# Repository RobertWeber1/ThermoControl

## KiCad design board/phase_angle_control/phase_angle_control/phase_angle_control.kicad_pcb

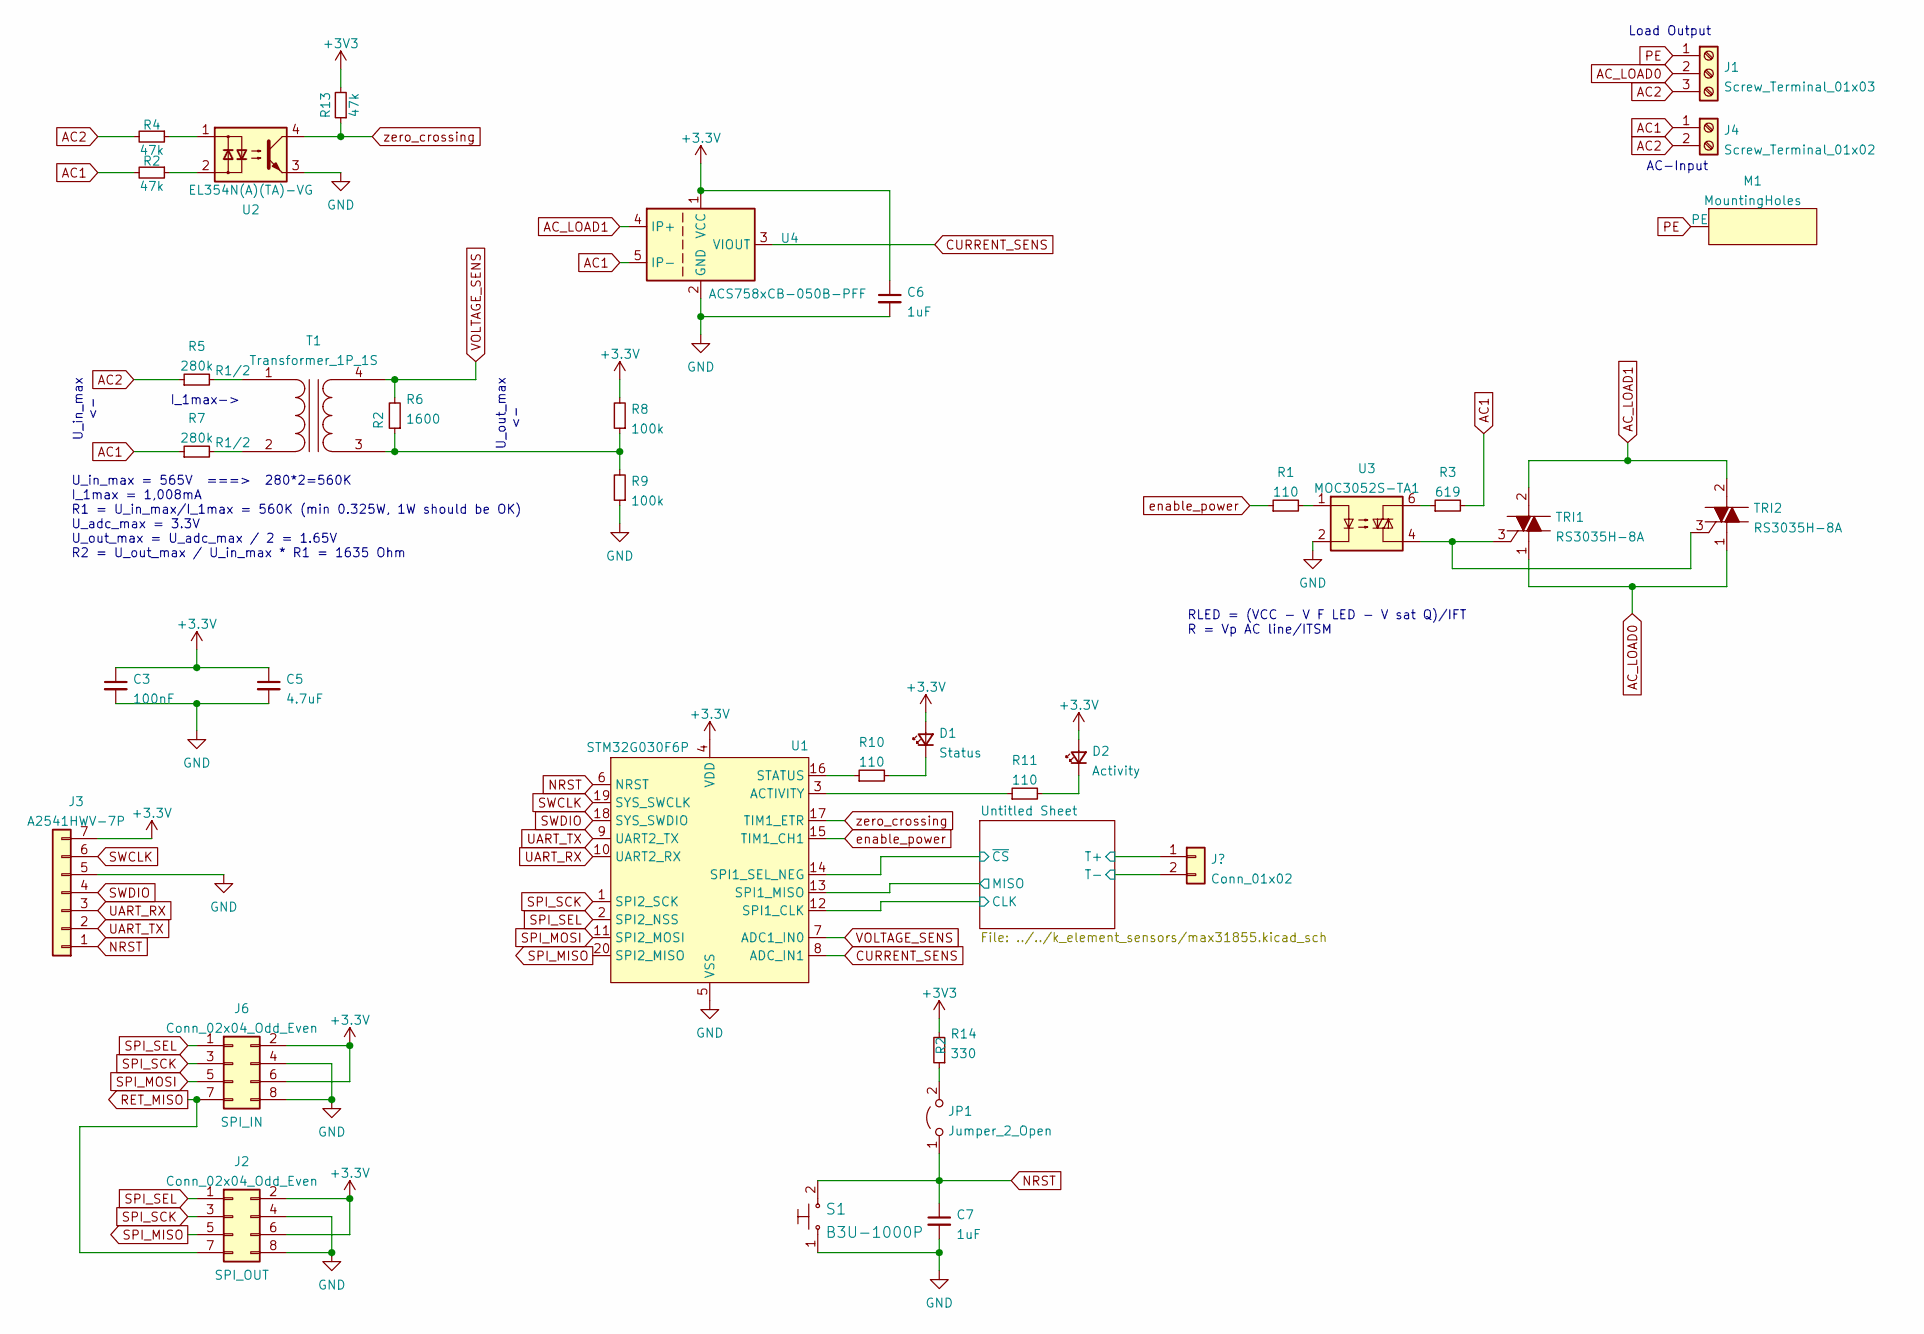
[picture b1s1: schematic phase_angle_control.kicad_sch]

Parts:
C3: 100nF; C_0603_1608Metric_Pad1.08x0.95mm_HandSolder; LCSC Part# C191538
C5: 4.7uF; C_0603_1608Metric_Pad1.08x0.95mm_HandSolder; LCSC Part# C651001
C6, C7: 1uF; C_0603_1608Metric_Pad1.08x0.95mm_HandSolder; LCSC Part# C393692
D1: Status; LED_0603_1608Metric_Pad1.05x0.95mm_HandSolder; LCSC Part# C273616
D2: Activity; LED_0603_1608Metric_Pad1.05x0.95mm_HandSolder; LCSC Part# C192667
J1: Screw_Terminal_01x03; KF206B-7.5-3P; LCSC Part# C475240
J2, J6: Conn_02x04_Odd_Even; PinHeader_2x04_P2.54mm_Horizontal; LCSC Part# C358706
J3: A2541HWV-7P; PinSocket_1x07_P2.54mm_Vertical; LCSC Part# C225504
J4: Screw_Terminal_01x02; KF206B-7.5-2P; LCSC Part# C475239
JP1: Jumper_2_Open; SolderJumper-2_P1.3mm_Open_RoundedPad1.0x1.5mm
M1: MountingHoles; MountingHolesPE
R1, R10, R11: 110; R_0603_1608Metric_Pad0.98x0.95mm_HandSolder; LCSC Part# C203247
R2: 47k; R_1206_3216Metric_Pad1.30x1.75mm_HandSolder; LCSC Part# C104822
R3: 619; R_1206_3216Metric_Pad1.30x1.75mm_HandSolder; LCSC Part# C247212
R4: 47k; R_1206_3216Metric_Pad1.30x1.75mm_HandSolder
R5, R7: 280k; R_1210_3225Metric_Pad1.30x2.65mm_HandSolder; LCSC Part# C422336
R6: 1600; R_0603_1608Metric_Pad0.98x0.95mm_HandSolder; LCSC Part# C186398
R8, R9: 100k; R_0603_1608Metric_Pad0.98x0.95mm_HandSolder; LCSC Part# C203223
R13: 47k; R_0603_1608Metric_Pad0.98x0.95mm_HandSolder; LCSC Part# C427281
R14: 330; R_0603_1608Metric_Pad0.98x0.95mm_HandSolder; LCSC Part# C186383
S1: B3U-1000P; Switch_Tactile_SMD_B3U-1000P; MPN B3U-1000P; Digi-Key_PN SW1020CT-ND
T1: Transformer_1P_1S; Transformer_ZMPT107-1; LCSC Part# C125191
TRI1, TRI2: RS3035H-8A; TO-220-3; MPN BTA16-600BWRG; LCSC Part# C246522
U1: STM32G030F6P; SSOP-20_4.4x6.5mm_P0.65mm; LCSC Part# C724040
U2: EL354N(A)(TA)-VG; SMDIP-4_W7.62mm; LCSC Part# C146213
U3: MOC3052S-TA1; DIP-6_W8.89mm_SMDSocket_LongPads; LCSC Part# C115471
U4: ACS758xCB-050B-PFF; Allegro_CB_PFF; LCSC Part# C73426

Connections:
/Untitled Sheet/CLK: U1.12 (SPI1_CLK); also elsewhere on the board
/Untitled Sheet/MISO: U1.13 (SPI1_MISO); also elsewhere on the board
/Untitled Sheet/~CS: U1.14 (SPI1_SEL_NEG); also elsewhere on the board
AC1: J4.1, R2.2, R3.2, R7.1, U4.5 (IP-)
AC2: J1.3, J4.2, R4.2, R5.1
AC_LOAD0: J1.2, TRI1.1 (A1), TRI2.1 (A1)
AC_LOAD1: TRI1.2 (A2), TRI2.2 (A2), U4.4 (IP+)
CURRENT_SENS: U1.8 (ADC_IN1), U4.3 (VIOUT)
GND: C3.2, C5.2, C6.2, C7.2, J2.4, J2.8, J3.5, J6.4, J6.8, R9.1, S1.1, U1.5 (VSS), U2.3, U3.2, U4.2 (GND); also elsewhere on the board
NRST: C7.1, J3.1, JP1.1 (A), S1.2, U1.6 (NRST)
unnamed: D1.1 (K), R10.2
unnamed: JP1.2 (B), R14.1
unnamed: R1.2, U3.1
unnamed: R2.1, U2.2
unnamed: R3.1, U3.6
unnamed: R4.1, U2.1
unnamed: R5.2, T1.1 (AA)
unnamed: R6.1, R8.1, R9.2, T1.3 (SA)
unnamed: R7.2, T1.2 (AB)
unnamed: R10.1, U1.16 (STATUS)
unnamed: R11.1, U1.3 (ACTIVITY)
unnamed: D2.1 (K), R11.2
unnamed: TRI1.3 (G), TRI2.3 (G), U3.4
PE: J1.1, M1.1 (PE)
RET_MISO: J2.7, J6.7
SPI_MISO: J2.5, U1.20 (SPI2_MISO)
SPI_MOSI: J6.5, U1.11 (SPI2_MOSI)
SPI_SCK: J2.3, J6.3, U1.1 (SPI2_SCK)
SPI_SEL: J2.1, J6.1, U1.2 (SPI2_NSS)
SWCLK: J3.6, U1.19 (SYS_SWCLK)
SWDIO: J3.4, U1.18 (SYS_SWDIO)
UART_RX: J3.3, U1.10 (UART2_RX)
UART_TX: J3.2, U1.9 (UART2_TX)
VOLTAGE_SENS: R6.2, T1.4 (SB), U1.7 (ADC1_IN0)
enable_power: R1.1, U1.15 (TIM1_CH1)
zero_crossing: R13.1, U1.17 (TIM1_ETR), U2.4

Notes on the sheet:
U_in_max = 565V ===> 280*2=560K I_1max = 1,008mA R1 = U_in_max/I_1max = 560K (min 0.325W, 1W should be OK) U_adc_max = 3.3V U_out_max = U_adc_max / 2 = 1.65V R2 = U_out_max / U_in_max * R1 = 1635 Ohm
U_in_max <-
I_1max->
U_out_max <-
RLED = (VCC - V F LED - V sat Q)/IFT R = Vp AC line/ITSM
Load Output
AC-Input

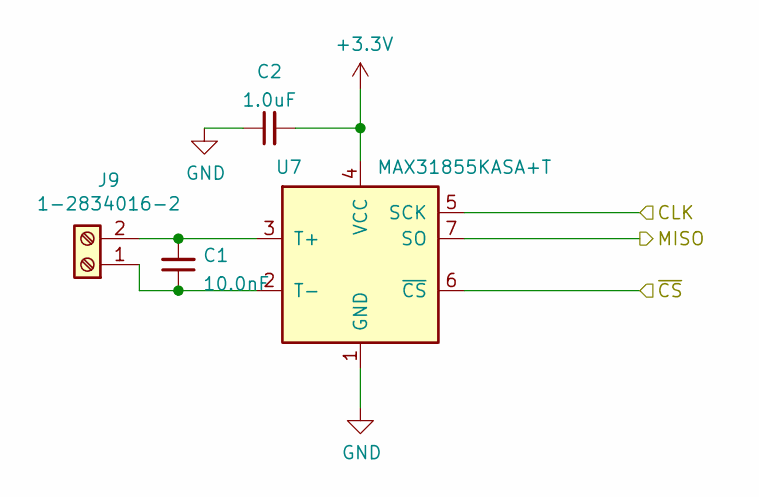
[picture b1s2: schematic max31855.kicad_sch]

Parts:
C1: 10.0nF; C_0603_1608Metric_Pad1.08x0.95mm_HandSolder; LCSC Part# C389113
C2: 1.0uF; C_0603_1608Metric_Pad1.08x0.95mm_HandSolder; LCSC Part# C328910
J9: 1-2834016-2; con_A123829-ND‎; LCSC Part # C474892
U7: MAX31855KASA+T; SOIC-8_3.9x4.9mm_P1.27mm; LCSC Part# C52028

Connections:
/Untitled Sheet/CLK: U7.5 (SCK); also elsewhere on the board
/Untitled Sheet/MISO: U7.7 (SO); also elsewhere on the board
/Untitled Sheet/~CS: U7.6 (~CS); also elsewhere on the board
GND: C2.1, U7.1 (GND); also elsewhere on the board
unnamed: C1.1, J9.1, U7.2 (T-)
unnamed: C1.2, J9.2, U7.3 (T+)

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
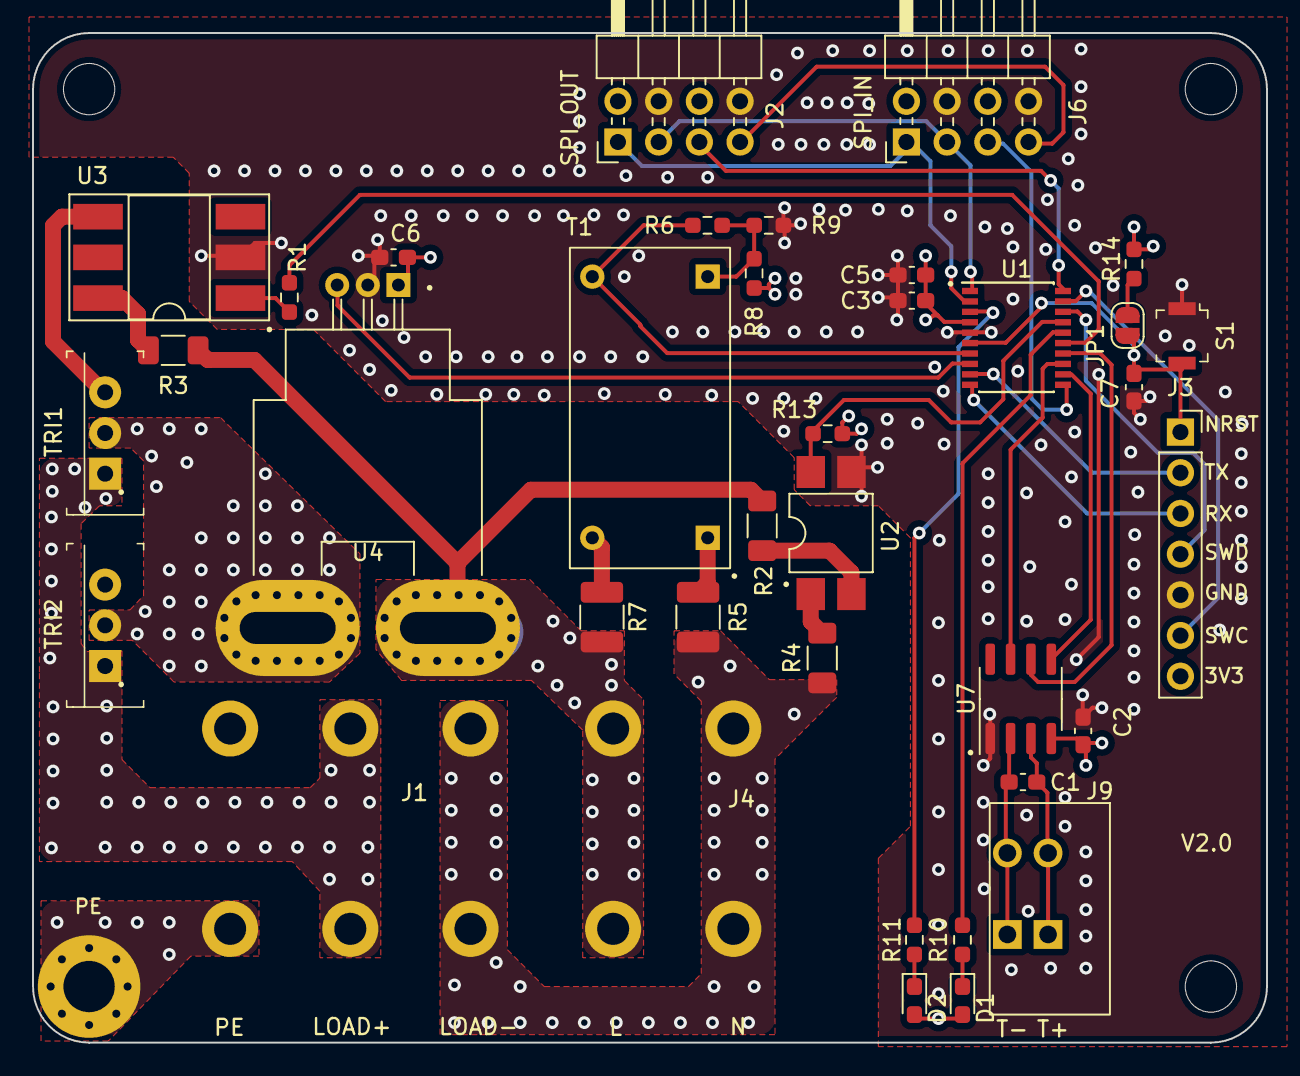
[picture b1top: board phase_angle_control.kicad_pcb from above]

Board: 4 copper layers, 77.0 x 63.0 mm, 38 parts (0 on the bottom side), 39 nets.

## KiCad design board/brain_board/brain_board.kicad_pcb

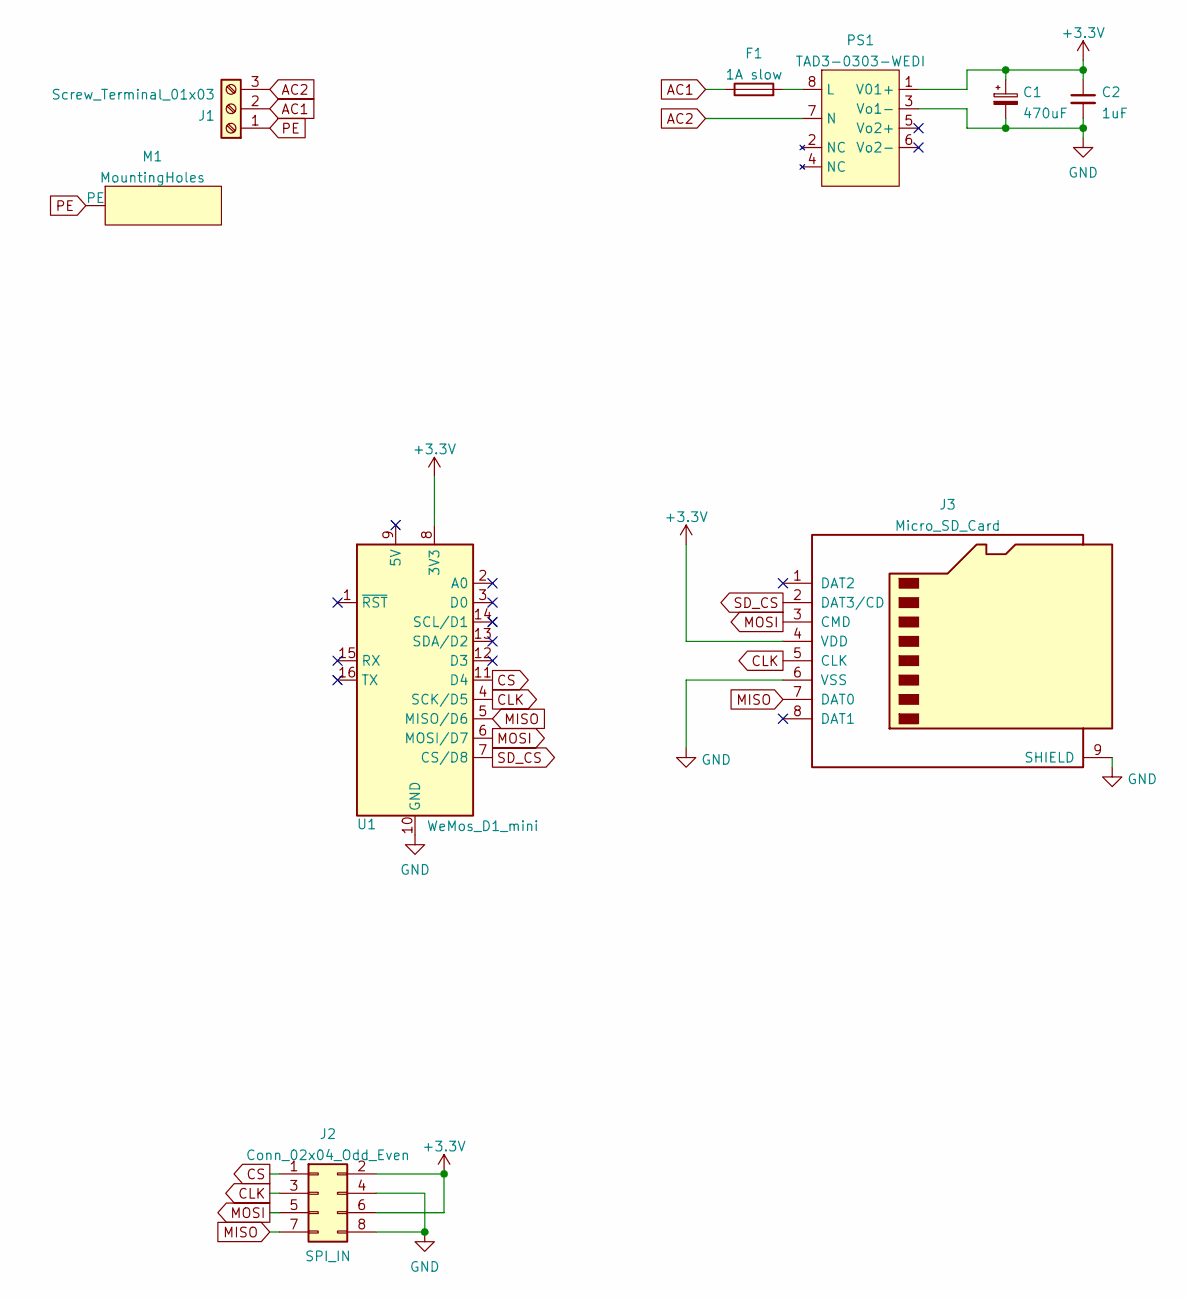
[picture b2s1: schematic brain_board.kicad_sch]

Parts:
C1: 470uF; CP_Radial_D8.0mm_P3.50mm; LCSC Part# C840136
C2: 1uF; C_Disc_D4.3mm_W1.9mm_P5.00mm; LCSC Part# C444742
F1: 1A slow; Fuse_2410; LCSC Part# C136380
J1: Screw_Terminal_01x03; KF206B-7.5-3P; LCSC Part# C475240
J2: Conn_02x04_Odd_Even; PinHeader_2x04_P2.54mm_Horizontal; LCSC Part# C358706
J3: Micro_SD_Card; micro_sd_slot; LCSC Part# C341095
M1: MountingHoles; MountingHolesPE
PS1: TAD3-0303-WEDI; LCSC Part# C695893
U1: WeMos_D1_mini; WEMOS_D1_mini_light

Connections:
+3V3: C1.1, C2.1, J2.2, J2.6, J3.4 (VDD), PS1.1 (V01+), U1.8 (3V3)
AC1: F1.1, J1.2
AC2: J1.3, PS1.7 (N)
CLK: J2.3, J3.5 (CLK), U1.4 (SCK/D5)
CS: J2.1, U1.11 (D4)
GND: C1.2, C2.2, J2.4, J2.8, J3.6 (VSS), J3.9 (SHIELD), PS1.3 (Vo1-), U1.10 (GND)
MISO: J2.7, J3.7 (DAT0), U1.5 (MISO/D6)
MOSI: J2.5, J3.3 (CMD), U1.6 (MOSI/D7)
unnamed: F1.2, PS1.8 (L)
PE: J1.1, M1.1 (PE)
SD_CS: J3.2 (DAT3/CD), U1.7 (CS/D8)

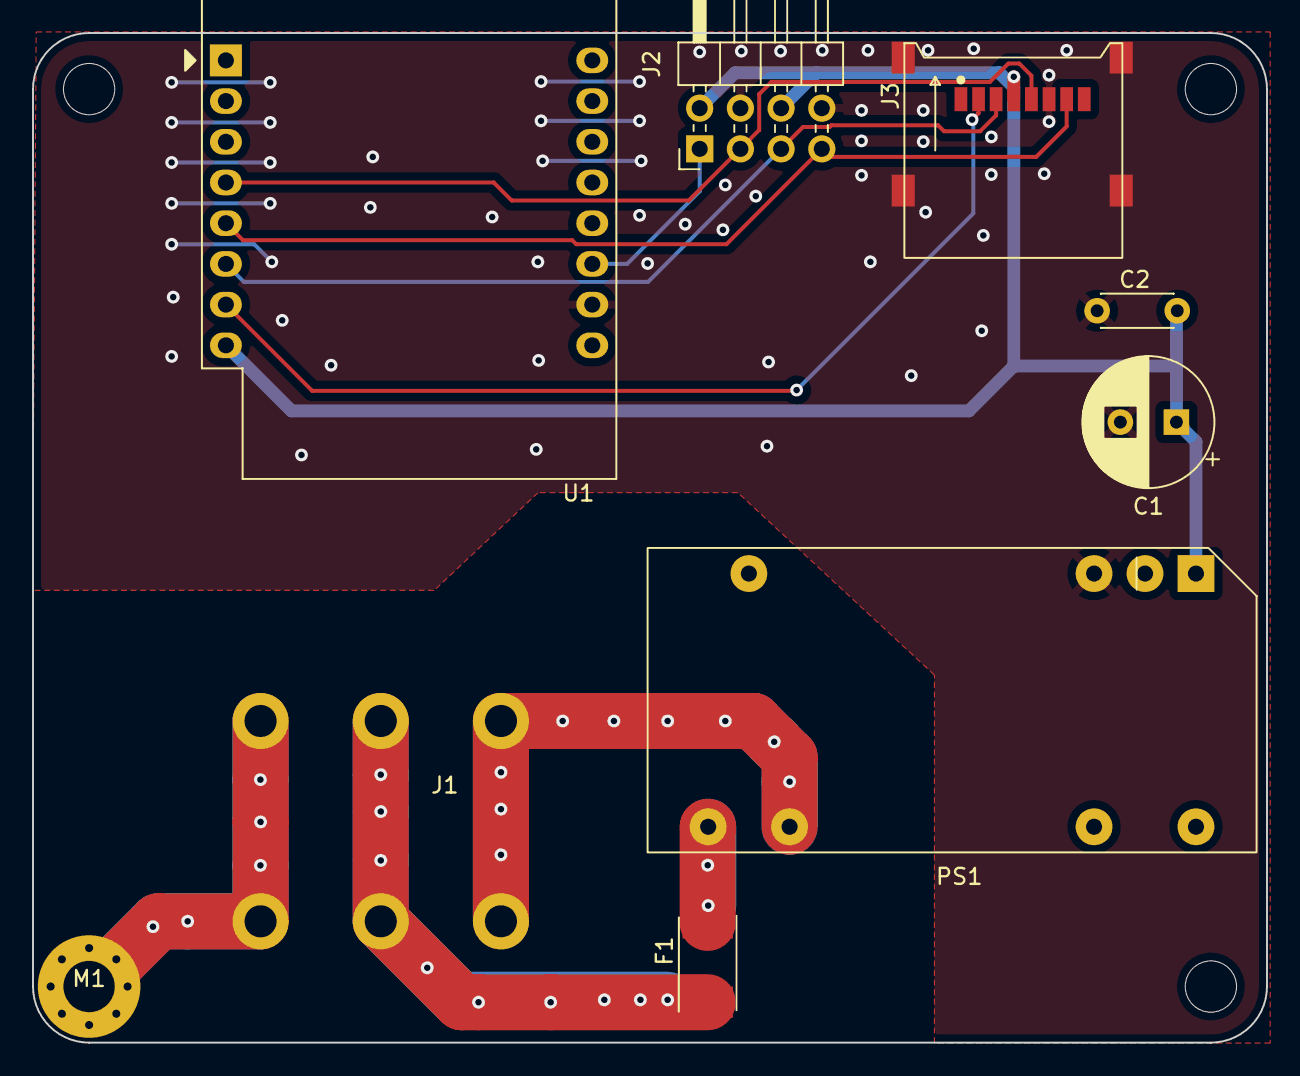
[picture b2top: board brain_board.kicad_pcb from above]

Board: 2 copper layers, 77.0 x 63.0 mm, 9 parts (0 on the bottom side), 11 nets.

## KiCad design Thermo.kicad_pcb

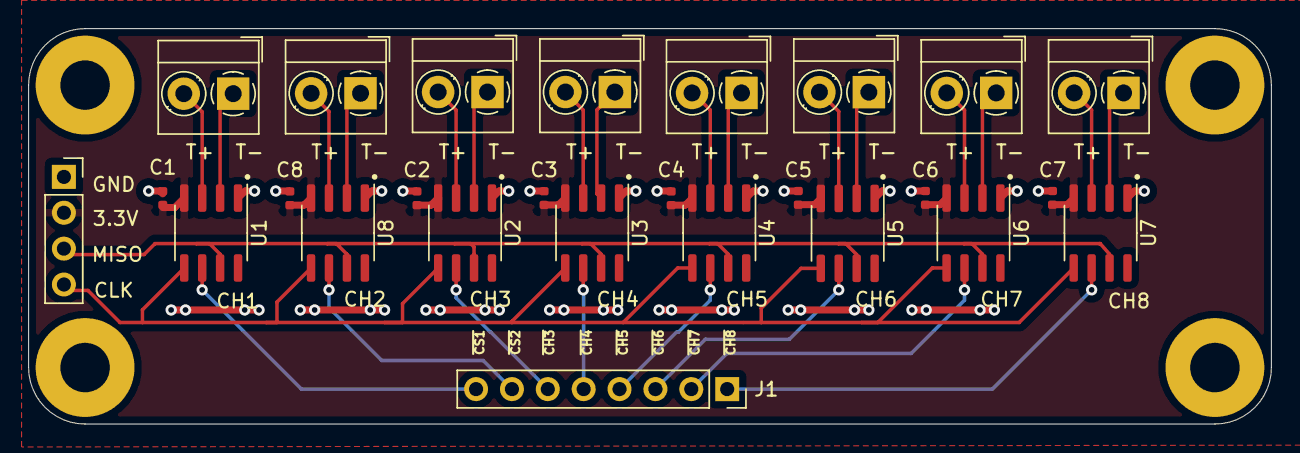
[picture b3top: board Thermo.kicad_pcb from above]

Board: 2 copper layers, 88.0 x 28.0 mm, 27 parts (0 on the bottom side), 28 nets.

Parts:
C1, C2, C3, C4, C5, C6, C7, C8: 0402_1.0uF__105_10%_25V; C_0402_1005Metric
H1: MountingHoles; MountingHole_pattern
J1: Conn_01x08; PinSocket_1x08_P2.54mm_Vertical
J2: Conn_01x04; PinSocket_1x04_P2.54mm_Vertical
J3, J4, J5, J6, J7, J8, J9, J10: Screw_Terminal_01x02; TerminalBlock_MetzConnect_Type059_RT06302HBWC_1x02_P3.50mm_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
U1, U2, U3, U4, U5, U6, U7, U8: MAX31855KASA+T; SOIC-8_3.9x4.9mm_P1.27mm

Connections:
+3V3: C1.2, C2.2, C3.2, C4.2, C5.2, C6.2, C7.2, C8.2, J2.2, U1.4, U2.4, U3.4, U4.4, U5.4, U6.4, U7.4, U8.4
/max31855/CLK: J2.4, U1.5, U2.5, U3.5, U4.5, U5.5, U6.5, U7.5, U8.5
/max31855/MISO: J2.3, U1.7, U2.7, U3.7, U4.7, U5.7, U6.7, U7.7, U8.7
/max31855/~CS~: J1.8, U1.6
/sheet606BA990/~CS~: J1.7, U8.6
/sheet606BAB02/~CS~: J1.6, U2.6
/sheet606BABA0/~CS~: J1.5, U3.6
/sheet606BAC16/~CS~: J1.4, U4.6
/sheet606BAC84/~CS~: J1.3, U5.6
/sheet606BACD6/~CS~: J1.2, U6.6
/sheet606BAD28/~CS~: J1.1, U7.6
GND: C1.1, C2.1, C3.1, C4.1, C5.1, C6.1, C7.1, C8.1, J2.1, U1.1, U2.1, U3.1, U4.1, U5.1, U6.1, U7.1, U8.1
unnamed: J3.1, U1.2
unnamed: J3.2, U1.3
unnamed: J4.1, U2.2
unnamed: J4.2, U2.3
unnamed: J5.1, U3.2
unnamed: J5.2, U3.3
unnamed: J6.1, U4.2
unnamed: J6.2, U4.3
unnamed: J7.1, U5.2
unnamed: J7.2, U5.3
unnamed: J8.1, U6.2
unnamed: J8.2, U6.3
unnamed: J9.1, U7.2
unnamed: J9.2, U7.3
unnamed: J10.1, U8.2
unnamed: J10.2, U8.3

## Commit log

2021-08-11 Restructure repo
2021-08-11 Add software
2021-08-27 Add phase angle controller board
2021-09-04 WIP GUI foo
2021-09-04 WIP2
2021-09-04 Wip3
2021-09-15 Working UART and SPI
2021-09-23 Add Arduino skatch
2021-09-23 Fix compiler warnings
2021-09-23 Working persistence layer
2021-09-23 Add SPI communicaion master test
2021-09-24 Reduce debug noise
2021-09-24 Implement new SPI data transfer
2021-10-04 Redesign phase angle contrller board for more current throughput
2021-10-10 Update phase-angle-control-board to handle more current
2021-10-10 Add base board for ESP8266
2021-10-10 Move arduino skatch
2021-10-10 Basic SPI communication between ESP8266 and PACs
2021-10-10 Start to improve spi abstraction
2021-10-20 Try to fix sd-card storage
2021-10-20 Increase spi transaction speed
2021-10-20 Start to implement SPI abstraction layer
2021-10-20 Split spi abstaction into multiple files
2021-10-20 Fix som formating
2021-11-07 WIP: Try cmake arduino
2021-11-07 Fix SD-Slot pin alignment
2021-11-07 Fix LED rotation
2021-11-07 Improve GUI, add input for max_on_time
2021-11-07 HAL: Add LED abstraction
